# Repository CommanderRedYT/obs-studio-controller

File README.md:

# obs-studio-controller
DIY hardware + software to control obs studio

## What is this?
This project will be a do-it-yourself solution to control OBS Studio.

It will have a custom PCB, based on the ESP32, with rotary encoders, buttons and and optional tft display.
I am planning on having a NodeJS backend as there are already great librarys to connect to OBS Studio!
The backend will also host a website to configure the device.

I am also planning on making a Video series showing my path on creating this project.

Tl;Dr:

## Features

- [ ] Custom PCB containing digital and analog inputs, based on the Espressif 32 Microcontroller.
- [ ] A 3D printable housing for the electronics
- [ ] NodeJS backend for configuring or updating the device

More will be added after designing and testing!

## Updating
I am planning to implement Over The Air Updates as well as flashing via USB C.

The ESP32 software will be using the ESP-IDF. From experience I have noticed some usability problems, so I will be using GitHub CI to build and then host the binaries.

## Contributing
If you encounter any problems, or have improvements, feel free to open an Issue or even a Pull Request!

## "Roadmap"
- After ordering the [first version](https://github.com/CommanderRedYT/obs-studio-controller/releases/tag/ordered-01) I discovered that I accidentally selected the wrong part for the rotary encoders (ones without buttons). Next revision will have that fixed, but for now, I will need to reorder the right components and try to replace the ones on the pcb

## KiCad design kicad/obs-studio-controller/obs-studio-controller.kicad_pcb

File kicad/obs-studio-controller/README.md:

# pcb

## Version 0.1 (Routing complete)

## Version 1.0 (PCB complete)

## Version 1.1 (Fix wrong rotary encoder)

## Version 1.2 (Fix flipped display header)

## Version 2.0 (Actually connect the rotary encoders)

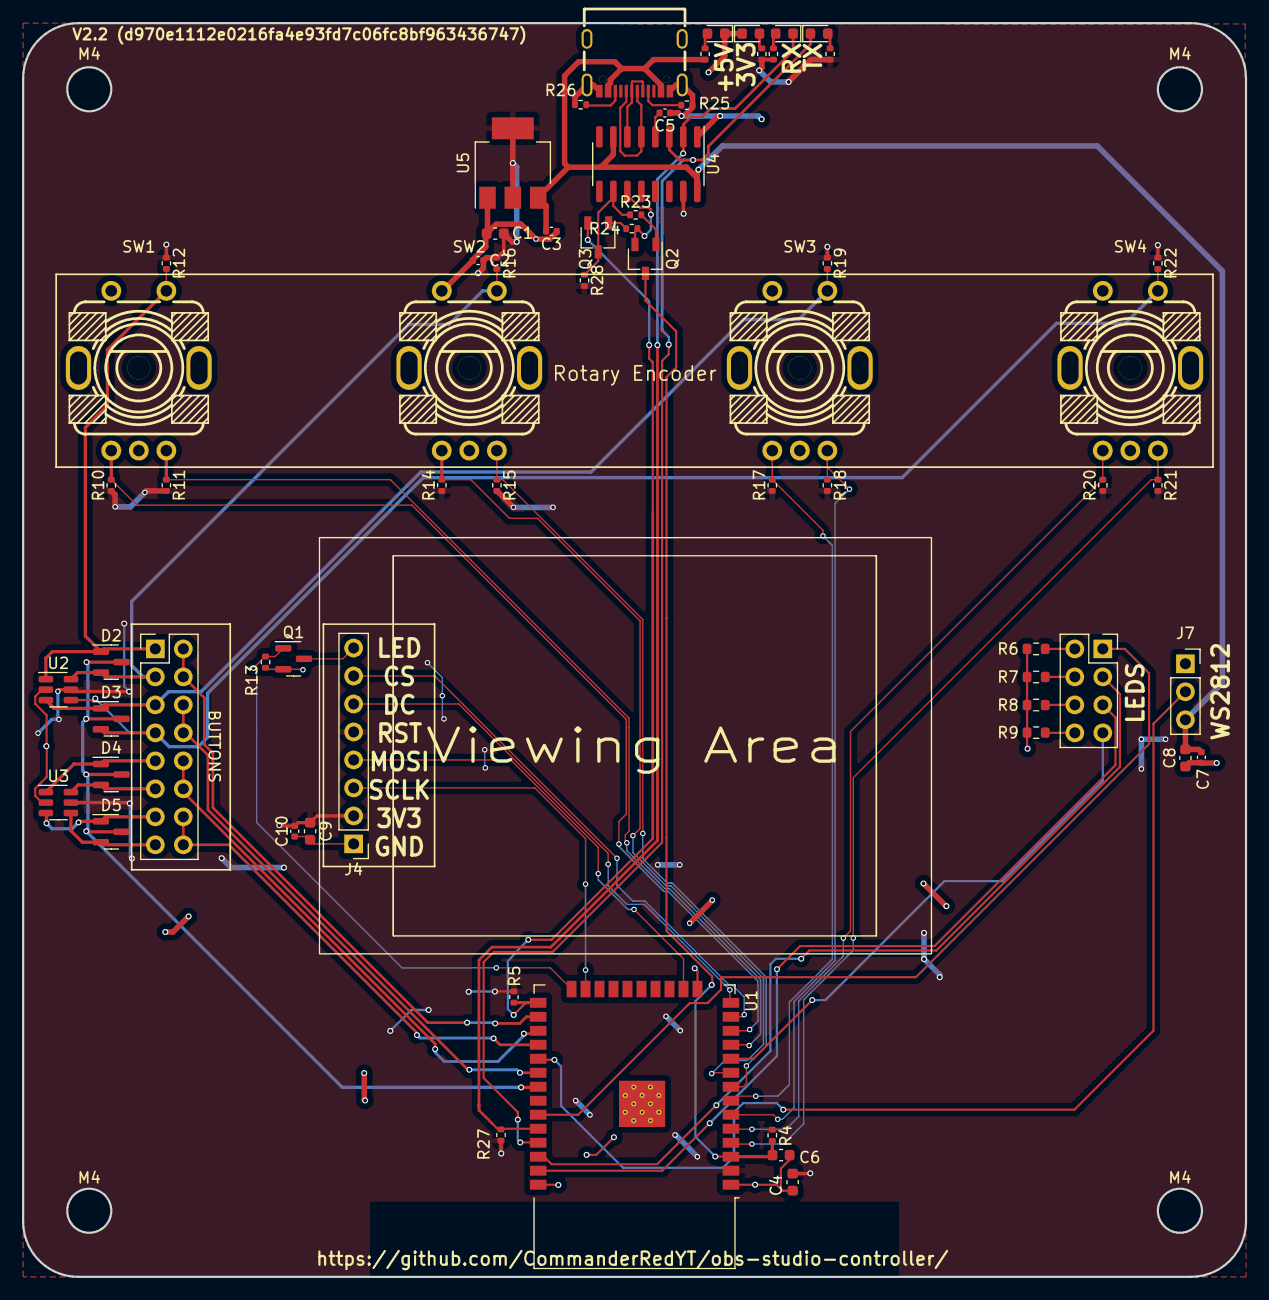
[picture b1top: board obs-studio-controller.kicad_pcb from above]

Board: 2 copper layers, 111.0 x 113.8 mm, 64 parts (0 on the bottom side), 56 nets.

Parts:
C1, C6, C8, C9: 10u; C_0603_1608Metric
C2, C3, C5, C7, C10: 100n; C_0402_1005Metric
C4: 1u; C_0603_1608Metric
D2, D3, D4, D5: BAV99; SOT-23
D6, D7, D8: LED; LED_0603_1608Metric
D9: LED5V; LED_0603_1608Metric
J3: LEDS; PinSocket_2x04_P2.54mm_Vertical
J4: Conn_Display; DISPLAY
J5: BUTTONS; PinHeader_2x08_P2.54mm_Vertical
J7: WS2812; PinSocket_1x03_P2.54mm_Vertical
Q1: 2N7002; SOT-23
Q2, Q3: SS8050_C2150; TSOT-23
R4, R5, R29, R30, R31, R32: 1k; R_0402_1005Metric
R6, R7, R8, R9: 100r; R_0603_1608Metric
R10, R11, R12, R13, R14, R15, R16, R17, R18, R19, R20, R21, R22, R27, R28: 10k; R_0402_1005Metric
R23, R24: 12k; R_0402_1005Metric
R25, R26: 5k1; R_0402_1005Metric
SW1, SW2, SW3, SW4: RotaryEncoder_Switch; SW-TH_EC11K1524406
U1: ESP32-WROOM-32
U2, U3: USBLC6-4SC6; SOT-23-6
U4: CH343G; SOIC-16_3.9x9.9mm_P1.27mm
U5: AMS1117-3.3; SOT-223-3_TabPin2
USBC1: MC-311D; USB-C-SMD_MC-311D

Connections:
+3V3: C1.2, C2.2, C4.2, C9.1, C10.2, J4.2, J4.5, R4.1, R5.1, R10.1, R11.2, R12.1, R14.1, R15.2, R16.1, R17.1, R18.2, R19.1, R20.1, R21.2, R22.1, R27.2, R28.2, R29.1, R30.1, R31.1, U1.2 (VDD), U2.5 (VBUS), U3.5 (VBUS), U4.15 (VIO), U5.2 (VO)
/AMS1117-5V-3v3/5V: C3.2, C7.2, C8.2, J7.3, R32.1, U4.7 (VBUS), U4.16 (VDD5), U5.3 (VI), USBC1.A4-B9 (VBUS), USBC1.B4-A9 (VBUS)
/BTN_IN1: J5.2, J5.4, U1.26 (IO4)
/BTN_IN2: J5.6, J5.8, U1.30 (IO18)
/BTN_IN3: J5.10, J5.12, U1.27 (IO16)
/BTN_IN4: J5.14, J5.16, U1.28 (IO17)
/BTN_OUT: D2.3 (K), D3.3 (K), D4.3 (K), D5.3 (K), U1.31 (IO19)
/BUTTON_1: D2.1 (K), J5.1, R12.2, SW1.E, U2.1 (I/O1)
/BUTTON_2: D2.2 (A), J5.3, R16.2, SW2.E, U2.6 (I/O4)
/BUTTON_3: D3.1 (K), J5.5, R19.2, SW3.E, U2.3 (I/O2)
/BUTTON_4: D3.2 (A), J5.7, R22.2, SW4.E, U2.4 (I/O3)
/Buttons/BUTTON_5: D4.1 (K), J5.9, U3.1 (I/O1)
/Buttons/BUTTON_6: D4.2 (A), J5.11, U3.6 (I/O4)
/Buttons/BUTTON_7: D5.1 (K), J5.13, U3.3 (I/O2)
/Buttons/BUTTON_8: D5.2 (A), J5.15, U3.4 (I/O3)
/DISPLAY_CS: J4.7, U1.13 (IO14)
/DISPLAY_DC: J4.6, U1.14 (IO12)
/DISPLAY_LED: Q1.1 (G), R13.1, U1.24 (IO2)
/DISPLAY_MOSI: J4.4, U1.16 (IO13)
/DISPLAY_SCLK: J4.3, U1.23 (IO15)
/Flasher/DTR: Q3.3 (C), R23.1, R28.1, U4.10 (~DTR/TNOW)
/Flasher/ESP_EN: C6.2, Q2.3 (C), R4.2, U1.3 (EN)
/Flasher/ESP_IO0: Q3.2 (E), R5.2, U1.25 (IO0)
/Flasher/ESP_RX: D6.1 (K), R27.1, U1.34 (RXD0/IO3), U4.2 (TXD)
/Flasher/ESP_TX: D7.1 (K), U1.35 (TXD0/IO1), U4.3 (RXD)
/Flasher/RTS: Q2.2 (E), R24.1, U4.11 (~RTS)
/Flasher/USB_DN: U4.6 (UD-), USBC1.A7 (DN1), USBC1.B7 (DN2)
/Flasher/USB_DP: U4.5 (UD+), USBC1.A6 (DP1), USBC1.B6 (DP2)
/IO5: J7.2, U1.29 (IO5)
/ROT1_CLK: R11.1, SW1.B, U1.11 (IO26)
/ROT1_DT: R10.2, SW1.A, U1.12 (IO27)
/ROT2_CLK: R15.1, SW2.B, U1.8 (IO32)
/ROT2_DT: R14.2, SW2.A, U1.9 (IO33)
/ROT3_CLK: R18.1, SW3.B, U1.6 (IO34)
/ROT3_DT: R17.2, SW3.A, U1.7 (IO35)
/ROT4_CLK: R21.1, SW4.B, U1.4 (SENSOR_VP)
/ROT4_DT: R20.2, SW4.A, U1.5 (SENSOR_VN)
GND: C1.1, C2.1, C3.1, C4.1, C5.1, C6.1, C7.1, C8.1, C9.2, C10.1, D8.1 (K), D9.1 (K), J4.1, J7.1, Q1.2 (S), R6.1, R7.1, R8.1, R9.1, R13.2, R25.2, R26.1, SW1.C, SW1.D, SW2.C, SW2.D, SW3.C, SW3.D, SW4.C, SW4.D, U1.1 (GND), U1.15 (GND), U1.38 (GND), U1.39 (GND), U2.2 (GND), U3.2 (GND), U4.1 (GND), U5.1 (GND), USBC1.1 (SHIELD), USBC1.2 (SHIELD), USBC1.3 (SHIELD), USBC1.4 (SHIELD), USBC1.A1-B12 (GND), USBC1.B1-A12 (GND)
unnamed: C5.2, U4.4 (V3)
unnamed: D6.2 (A), R29.2
unnamed: D7.2 (A), R30.2
unnamed: D8.2 (A), R31.2
unnamed: D9.2 (A), R32.2
unnamed: J3.1, U1.33 (IO21)
unnamed: J3.2, R6.2
unnamed: J3.3, U1.36 (IO22)
unnamed: J3.4, R7.2
unnamed: J3.5, U1.37 (IO23)
unnamed: J3.6, R8.2
unnamed: J3.7, U1.10 (IO25)
unnamed: J3.8, R9.2
unnamed: J4.8, Q1.3 (D)
unnamed: Q2.1 (B), R23.2
unnamed: Q3.1 (B), R24.2
unnamed: R25.1, USBC1.A5 (CC1)
unnamed: R26.2, USBC1.B5 (CC2)

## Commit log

2022-12-30 Added initial schematic
2022-12-30 Placed parts in pcb layout, nothing moved yet
2022-12-31 Routing complete
2022-12-31 Added picture
2022-12-31 Added readme
2023-01-01 Fixed label, changed edge cuts, added screw holes
2023-01-01 Added some labels
2023-01-01 Updated readme / screenshots
2023-01-01 Updated production files
2023-01-02 Added step file
2023-01-02 Added rotary 3d model, discovered that the lcsc part number is wrong
2023-01-05 Fixed rotary encoder
2023-01-05 Updated paths
2023-01-05 Updated step
2023-01-13 Fix flipped display header
2023-01-14 Initial commit of firmware (Hello World working)
2023-01-14 Changed readme
2023-01-14 Removed files
2023-01-14 Added 3d printing files
2023-01-14 Forgot chmod +x
2023-01-14 Added icon converter and boot logo
2023-01-14 Fixed logo, successful boot
2023-01-15 Actually connect rotary encoder
2023-01-15 Forgot to add 3v3 trace
2023-01-15 Commited state
2023-01-16 Rotary is working
2023-01-16 Changed to bool literal
2023-04-08 Updated pcb
2023-04-08 Updated for production
